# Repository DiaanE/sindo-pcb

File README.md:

# Sindo

An open source full custom keyboard based on the Ergodox keyboards.

## Goal

The objective is to ultimately create a bluetooth low-profile switch version of the Ergodox, with a different layout for the thumbkeys. This design will probably not be RGB backlit, but that might change in the future. This project has no affiliation with Ergodox or ZSA.

## Hardware overview

The current goal is to use the ESP32-WROOM from Expressif, it has built-in bluetooth, a low-power processor and additional peripheral support via I2S and I2C that can later be used to drive a RGB matrix. It has enough IO to facilitate the scanning matrix. It is pretty easy to get your hands on one, and is very well priced for the massive feature set that it is comprised of. 

I am currently considering using blue low profile gateron switches. This is purely personal preference. There are also brown varieties in the same form factor.

## Software

Still considering whether or not to write my own firmware, fork an existing project or just make minimal customizations to and existing project. A few promising projects:

- https://github.com/asterics/esp32_mouse_keyboard
- https://github.com/Galzai/MK32

## Contributing

This is intented to be my personal keyboard, feel free to use this design as a base for your own, however, I cannot guarantee the stability of the designs in this repo. As such, I will not be accepting PR's or attending to issues :) This might change depending on the popularity of this project.

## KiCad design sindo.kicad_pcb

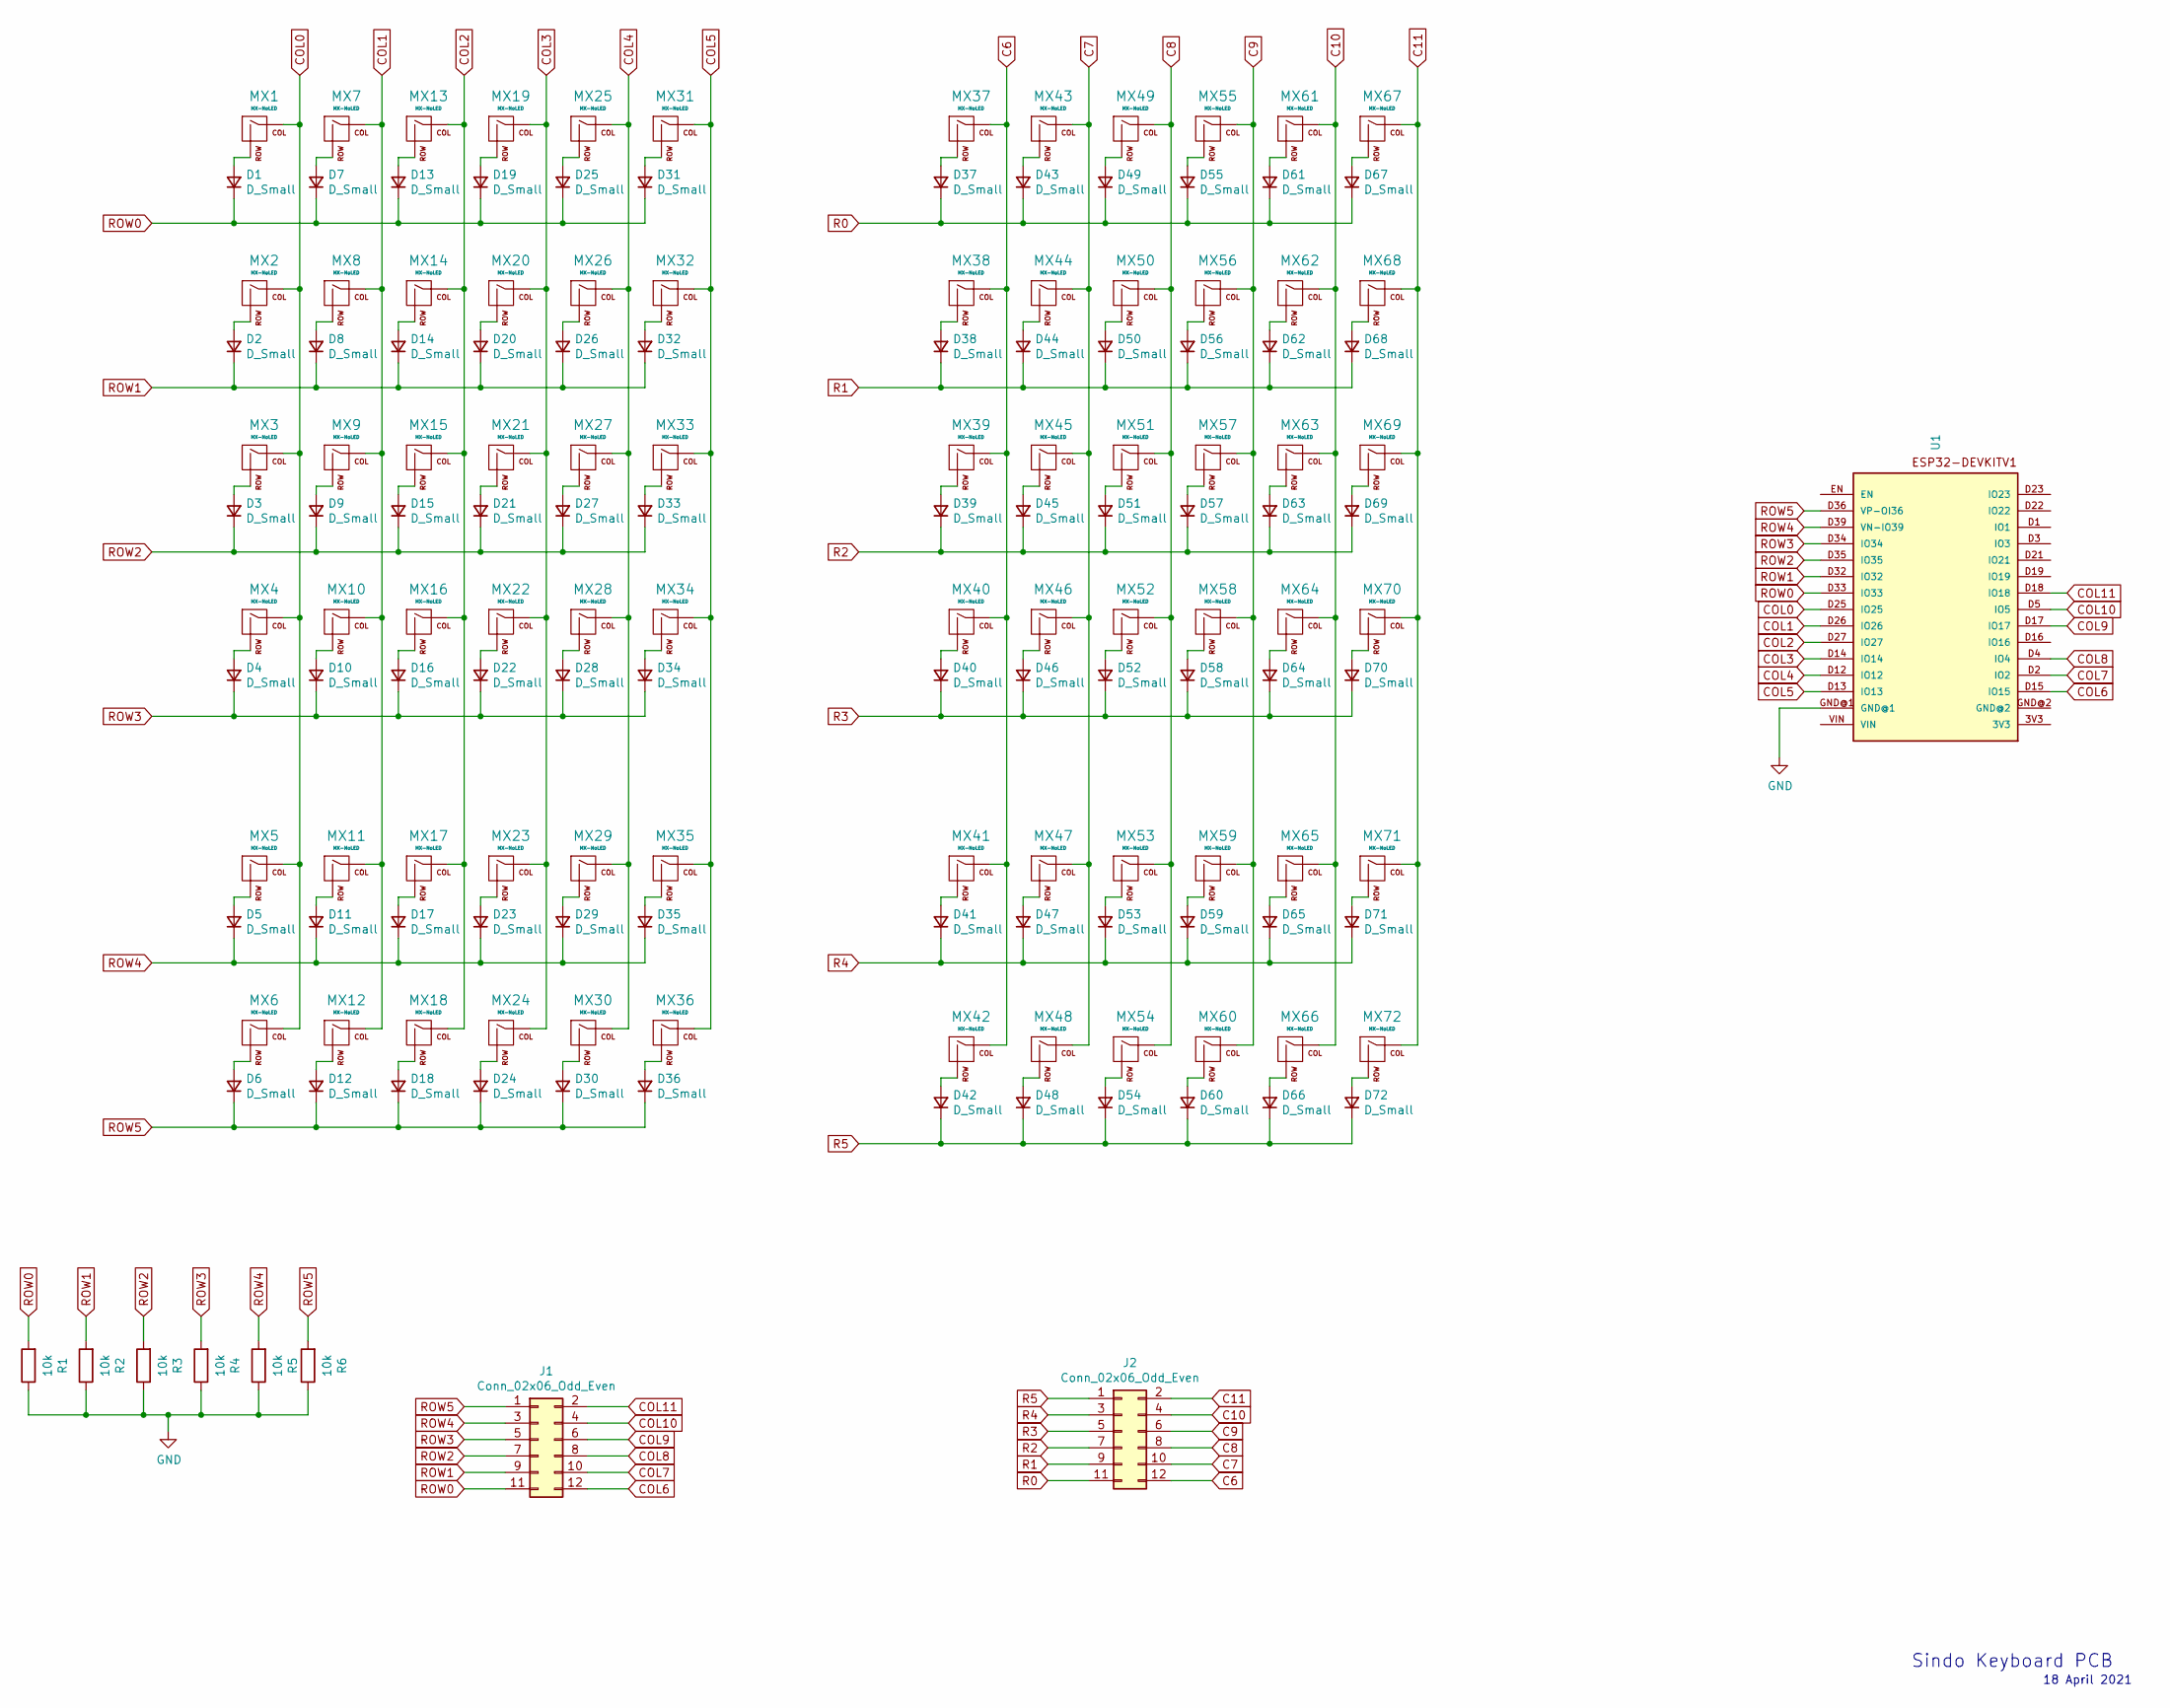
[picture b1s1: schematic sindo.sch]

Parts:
D1, D2, D3, D4, D5, D6, D7, D8, D9, D10, D11, D12, D13, D14, D15, D16, D17, D18, D19, D20, D21, D22, D23, D24, D25, D26, D27, D28, D29, D30, D31, D32, D33, D34, D35, D36, D37, D38, D39, D40, D41, D42, D43, D44, D45, D46, D47, D48, D49, D50, D51, D52, D53, D54, D55, D56, D57, D58, D59, D60, D61, D62, D63, D64, D65, D66, D67, D68, D69, D70, D71, D72: D_Small; D_DO-35_SOD27_P7.62mm_Horizontal
J1, J2: Conn_02x06_Odd_Even; PinHeader_2x06_P2.54mm_Vertical
MX1, MX2, MX3, MX4, MX5, MX6, MX7, MX8, MX9, MX10, MX11, MX12, MX13, MX14, MX15, MX16, MX17, MX18, MX19, MX20, MX21, MX22, MX23, MX24, MX25, MX26, MX27, MX28, MX29, MX30, MX31, MX32, MX33, MX34, MX35, MX36, MX37, MX38, MX39, MX40, MX41, MX42, MX43, MX44, MX45, MX46, MX47, MX48, MX49, MX50, MX51, MX52, MX53, MX54, MX55, MX56, MX57, MX58, MX59, MX60, MX61, MX62, MX63, MX64, MX65, MX66, MX67, MX68, MX69, MX70, MX71, MX72: MX-NoLED; MXOnly-1U-NoLED
R1, R2, R3, R4, R5, R6: 10k; R_Axial_DIN0411_L9.9mm_D3.6mm_P7.62mm_Vertical
U1: ESP32DEVKITV1; ESP32-DEVKITV1

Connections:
C6: J2.12, MX37.1 (COL), MX38.1 (COL), MX39.1 (COL), MX40.1 (COL), MX41.1 (COL), MX42.1 (COL)
C7: J2.10, MX43.1 (COL), MX44.1 (COL), MX45.1 (COL), MX46.1 (COL), MX47.1 (COL), MX48.1 (COL)
C8: J2.8, MX49.1 (COL), MX50.1 (COL), MX51.1 (COL), MX52.1 (COL), MX53.1 (COL), MX54.1 (COL)
C9: J2.6, MX55.1 (COL), MX56.1 (COL), MX57.1 (COL), MX58.1 (COL), MX59.1 (COL), MX60.1 (COL)
C10: J2.4, MX61.1 (COL), MX62.1 (COL), MX63.1 (COL), MX64.1 (COL), MX65.1 (COL), MX66.1 (COL)
C11: J2.2, MX67.1 (COL), MX68.1 (COL), MX69.1 (COL), MX70.1 (COL), MX71.1 (COL), MX72.1 (COL)
COL0: MX1.1 (COL), MX2.1 (COL), MX3.1 (COL), MX4.1 (COL), MX5.1 (COL), MX6.1 (COL), U1.D25 (IO25)
COL1: MX7.1 (COL), MX8.1 (COL), MX9.1 (COL), MX10.1 (COL), MX11.1 (COL), MX12.1 (COL), U1.D26 (IO26)
COL2: MX13.1 (COL), MX14.1 (COL), MX15.1 (COL), MX16.1 (COL), MX17.1 (COL), MX18.1 (COL), U1.D27 (IO27)
COL3: MX19.1 (COL), MX20.1 (COL), MX21.1 (COL), MX22.1 (COL), MX23.1 (COL), MX24.1 (COL), U1.D14 (IO14)
COL4: MX25.1 (COL), MX26.1 (COL), MX27.1 (COL), MX28.1 (COL), MX29.1 (COL), MX30.1 (COL), U1.D12 (IO12)
COL5: MX31.1 (COL), MX32.1 (COL), MX33.1 (COL), MX34.1 (COL), MX35.1 (COL), MX36.1 (COL), U1.D13 (IO13)
COL6: J1.12, U1.D15 (IO15)
COL7: J1.10, U1.D2 (IO2)
COL8: J1.8, U1.D4 (IO4)
COL9: J1.6, U1.D17 (IO17)
COL10: J1.4, U1.D5 (IO5)
COL11: J1.2, U1.D18 (IO18)
GND: R1.1, R2.1, R3.1, R4.1, R5.1, R6.1, U1.GND@1
unnamed: D1.2 (A), MX1.2 (ROW)
unnamed: D2.2 (A), MX2.2 (ROW)
unnamed: D3.2 (A), MX3.2 (ROW)
unnamed: D4.2 (A), MX4.2 (ROW)
unnamed: D5.2 (A), MX5.2 (ROW)
unnamed: D6.2 (A), MX6.2 (ROW)
unnamed: D7.2 (A), MX7.2 (ROW)
unnamed: D8.2 (A), MX8.2 (ROW)
unnamed: D9.2 (A), MX9.2 (ROW)
unnamed: D10.2 (A), MX10.2 (ROW)
unnamed: D11.2 (A), MX11.2 (ROW)
unnamed: D12.2 (A), MX12.2 (ROW)
unnamed: D13.2 (A), MX13.2 (ROW)
unnamed: D14.2 (A), MX14.2 (ROW)
unnamed: D15.2 (A), MX15.2 (ROW)
unnamed: D16.2 (A), MX16.2 (ROW)
unnamed: D17.2 (A), MX17.2 (ROW)
unnamed: D18.2 (A), MX18.2 (ROW)
unnamed: D19.2 (A), MX19.2 (ROW)
unnamed: D20.2 (A), MX20.2 (ROW)
unnamed: D21.2 (A), MX21.2 (ROW)
unnamed: D22.2 (A), MX22.2 (ROW)
unnamed: D23.2 (A), MX23.2 (ROW)
unnamed: D24.2 (A), MX24.2 (ROW)
unnamed: D25.2 (A), MX25.2 (ROW)
unnamed: D26.2 (A), MX26.2 (ROW)
unnamed: D27.2 (A), MX27.2 (ROW)
unnamed: D28.2 (A), MX28.2 (ROW)
unnamed: D29.2 (A), MX29.2 (ROW)
unnamed: D30.2 (A), MX30.2 (ROW)
unnamed: D31.2 (A), MX31.2 (ROW)
unnamed: D32.2 (A), MX32.2 (ROW)
unnamed: D33.2 (A), MX33.2 (ROW)
unnamed: D34.2 (A), MX34.2 (ROW)
unnamed: D35.2 (A), MX35.2 (ROW)
unnamed: D36.2 (A), MX36.2 (ROW)
unnamed: D37.2 (A), MX37.2 (ROW)
unnamed: D38.2 (A), MX38.2 (ROW)
unnamed: D39.2 (A), MX39.2 (ROW)
unnamed: D40.2 (A), MX40.2 (ROW)
unnamed: D41.2 (A), MX41.2 (ROW)
unnamed: D42.2 (A), MX42.2 (ROW)
unnamed: D43.2 (A), MX43.2 (ROW)
unnamed: D44.2 (A), MX44.2 (ROW)
unnamed: D45.2 (A), MX45.2 (ROW)
unnamed: D46.2 (A), MX46.2 (ROW)
unnamed: D47.2 (A), MX47.2 (ROW)
unnamed: D48.2 (A), MX48.2 (ROW)
unnamed: D49.2 (A), MX49.2 (ROW)
unnamed: D50.2 (A), MX50.2 (ROW)
unnamed: D51.2 (A), MX51.2 (ROW)
unnamed: D52.2 (A), MX52.2 (ROW)
unnamed: D53.2 (A), MX53.2 (ROW)
unnamed: D54.2 (A), MX54.2 (ROW)
unnamed: D55.2 (A), MX55.2 (ROW)
unnamed: D56.2 (A), MX56.2 (ROW)
unnamed: D57.2 (A), MX57.2 (ROW)
unnamed: D58.2 (A), MX58.2 (ROW)
unnamed: D59.2 (A), MX59.2 (ROW)
unnamed: D60.2 (A), MX60.2 (ROW)
unnamed: D61.2 (A), MX61.2 (ROW)
unnamed: D62.2 (A), MX62.2 (ROW)
unnamed: D63.2 (A), MX63.2 (ROW)
unnamed: D64.2 (A), MX64.2 (ROW)
unnamed: D65.2 (A), MX65.2 (ROW)
unnamed: D66.2 (A), MX66.2 (ROW)
unnamed: D67.2 (A), MX67.2 (ROW)
unnamed: D68.2 (A), MX68.2 (ROW)
unnamed: D69.2 (A), MX69.2 (ROW)
unnamed: D70.2 (A), MX70.2 (ROW)
unnamed: D71.2 (A), MX71.2 (ROW)
unnamed: D72.2 (A), MX72.2 (ROW)
R0: D37.1 (K), D43.1 (K), D49.1 (K), D55.1 (K), D61.1 (K), D67.1 (K), J2.11
R1: D38.1 (K), D44.1 (K), D50.1 (K), D56.1 (K), D62.1 (K), D68.1 (K), J2.9
R2: D39.1 (K), D45.1 (K), D51.1 (K), D57.1 (K), D63.1 (K), D69.1 (K), J2.7
R3: D40.1 (K), D46.1 (K), D52.1 (K), D58.1 (K), D64.1 (K), D70.1 (K), J2.5
R4: D41.1 (K), D47.1 (K), D53.1 (K), D59.1 (K), D65.1 (K), D71.1 (K), J2.3
R5: D42.1 (K), D48.1 (K), D54.1 (K), D60.1 (K), D66.1 (K), D72.1 (K), J2.1
ROW0: D1.1 (K), D7.1 (K), D13.1 (K), D19.1 (K), D25.1 (K), D31.1 (K), J1.11, R1.2, U1.D33 (IO33)
ROW1: D2.1 (K), D8.1 (K), D14.1 (K), D20.1 (K), D26.1 (K), D32.1 (K), J1.9, R2.2, U1.D32 (IO32)
ROW2: D3.1 (K), D9.1 (K), D15.1 (K), D21.1 (K), D27.1 (K), D33.1 (K), J1.7, R3.2, U1.D35 (IO35)
ROW3: D4.1 (K), D10.1 (K), D16.1 (K), D22.1 (K), D28.1 (K), D34.1 (K), J1.5, R4.2, U1.D34 (IO34)
ROW4: D5.1 (K), D11.1 (K), D17.1 (K), D23.1 (K), D29.1 (K), D35.1 (K), J1.3, R5.2, U1.D39 (VN-IO39)
ROW5: D6.1 (K), D12.1 (K), D18.1 (K), D24.1 (K), D30.1 (K), D36.1 (K), J1.1, R6.2, U1.D36 (VP-OI36)

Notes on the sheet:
Sindo Keyboard PCB
18 April 2021

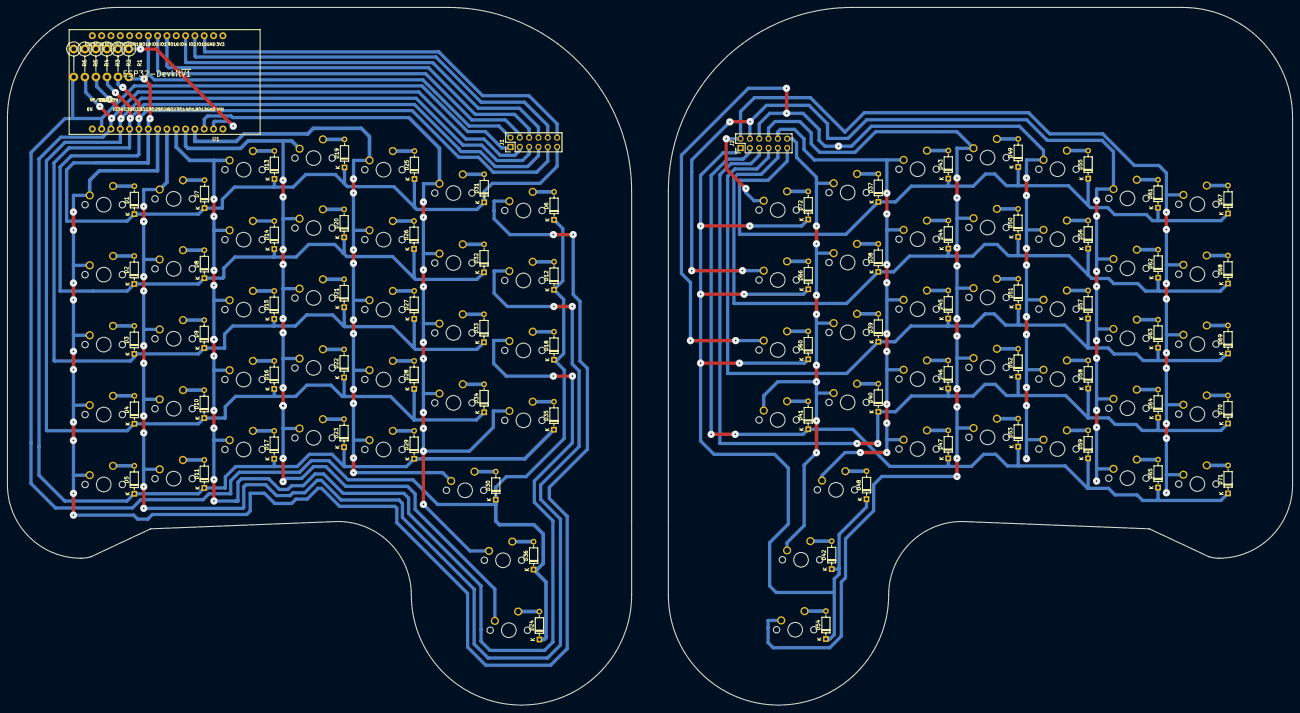
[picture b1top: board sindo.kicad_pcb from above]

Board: 2 copper layers, 350.0 x 190.0 mm, 153 parts (0 on the bottom side), 103 nets.

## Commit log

2021-04-04 Initial empty project
2021-04-04 Added some structure to the repo.
2021-04-04 Added a README to explain the libs folder.
2021-04-04 Ignoring the contents of libs.
2021-04-04 Basic overview of the project as it currently stands.
2021-04-18 Built the keyboard matrix and added MCU
2021-04-19 Finished lables, might still need pull-downs
2021-04-21 Added pull down resistors to rows
2021-04-21 Used a better header, linked schematic to footprints.
2021-04-21 Put footprints on PCB
2021-04-21 Started with the first half layout
2021-04-23 Almost done with layout
2021-04-23 Done with the basic layout
2021-04-23 Using a better header footprint.
2021-04-24 Reworked the layout for a single layer
2021-04-25 Finished the Sindo PCB V1
2021-04-27 Added ready to print bottom layers for toner transfer method.
2021-04-27 Added more realistic footprints for the headers and resistors
2021-04-27 Updated schematic to more realistic THT footprints
